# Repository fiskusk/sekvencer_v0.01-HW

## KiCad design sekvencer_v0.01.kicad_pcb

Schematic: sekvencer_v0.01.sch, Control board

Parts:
C1, C2, C4, C5, C9, C10: 10n; C_0805_2012Metric
C3: 47u; CP_Radial_D5.0mm_P2.50mm
C6, C23, C37: 1u; C_0805_2012Metric
C7, C8, C15, C17, C18, C20, C24, C25, C27: 100n; C_0805_2012Metric
C11, C12: 47n; C_0805_2012Metric
C13, C16, C19: 1n; C_0805_2012Metric
C14: 100p; C_0805_2012Metric
C21: 100u; CP_Radial_D10.0mm_P5.00mm
C22: 4u7; C_0805_2012Metric
C26: 470u; CP_Radial_D10.0mm_P5.00mm
C28, C29, C30, C33, C34, C36, C38, C39: NFM21CC223R1H3D; NFM21C_Series
C31, C32: 15p; C_0805_2012Metric
C35: 2u2; C_0805_2012Metric
D1: BAS7002VH6327XTSA1; D_SOD-523
D2: 1N4148; D_SOD-123
D3: LM4040DBZ-2.5; SOT-23
D4, D5: 1N4148; D_MELF
D6: STPS3L60U; D_SMB
D7: STAT1; LED_0805_2012Metric
D8: REL1; LED_0805_2012Metric
D9: REL2; LED_0805_2012Metric
D10: FAN; LED_0805_2012Metric
D11: +5V; LED_0805_2012Metric
D12: PTT; LED_0805_2012Metric
D13: 3.3V; LED_0805_2012Metric
D_50V1: LH R974-LP-1; LED_0805_2012Metric
J1: AVR_ISP_01X06; PinHeader_1x06_P2.54mm_Vertical
J2: PTT; JST_XH_B02B-XH-A_1x02_P2.50mm_Vertical
J3: SWR; JST_XH_B02B-XH-A_1x02_P2.50mm_Vertical
J4: PWR; JST_XH_B02B-XH-A_1x02_P2.50mm_Vertical
J5: LCD; JST_EH_B09B-EH-A_1x09_P2.50mm_Vertical
J6: RX_REL; JST_XH_B02B-XH-A_1x02_P2.50mm_Vertical
J7: TX_REL; JST_XH_B02B-XH-A_1x02_P2.50mm_Vertical
J8: FAN; JST_XH_B02B-XH-A_1x02_P2.50mm_Vertical
J9: 50V_IN; TerminalBlock_KEYS7808
J10: 50V_OUT; TerminalBlock_KEYS7808
J11: BIAS_DIRECT; JST_XH_B02B-XH-A_1x02_P2.50mm_Vertical
J12, J14, J15, J16, J18, J19: 50V_GND; MountingHole_3.2mm_M3_Pad_Via
J13: TERMISTOR; JST_XH_B02B-XH-A_1x02_P2.50mm_Vertical
J17: BIAS; JST_XH_B02B-XH-A_1x02_P2.50mm_Vertical
L1, L2: 470n; L_0805_2012Metric_Pad1.15x1.50mm_HandSolder
L3: 10u; L_0805_2012Metric
L4: DE1209-230u; L_12x12mm_H8mm
L5, L6, L7, L8, L9, L10: BLM31PG500SN1L; C_1206_3216Metric
Q1: BC857; SOT-23
Q2, Q3, Q6: BSS138; SOT-23
Q4: IRLML0030TRPBF; SOT-23
Q5: BBS3002-TL-1E; TO-263-2
Q7: BC847; TO-92
R1, R7, R8, R22: 4k7; R_0805_2012Metric
R2, R6, R9, R21, R26, R34: 1k; R_0805_2012Metric
R3, R14, R16: 10k; R_0805_2012Metric
R4, R5, R17: 22k; R_0805_2012Metric
R10, R11, R12, R18: 100k; R_0805_2012Metric
R13: 499R; R_0805_2012Metric
R15: 270k; R_0805_2012Metric
R19, R20: 0R005; OAR5R010FLF
R23: 100k; R_0402_1005Metric
R25: 1k2; R_0805_2012Metric
R27: 12k; R_0805_2012Metric
R28: 18k; R_0805_2012Metric
R29, R30, R31: 3k9; R_0805_2012Metric
R32: 2k2; R_0805_2012Metric
R33: 10R; R_0805_2012Metric
R35: 220R; R_0805_2012Metric
R36: 470R; R_0805_2012Metric
RV1, RV2, RV3, RV4: 10k; Potentiometer_Bourns_3214J_Horizontal
TP1: ADC_UCC; TestPoint_Pad_D2.0mm
TP2: +5V; TestPoint_Pad_D2.0mm
TP3: +12V; TestPoint_Pad_D2.0mm
TP4: ADC ICC; TestPoint_Pad_D2.0mm
TP5: GND; TestPoint_Pad_D2.0mm
U1: ATmega328P-AU; TQFP-32_7x7mm_P0.8mm
U2: LP2950-5.0_TO252; TO-252-2
U3: LM2576HVS-12; TO-263-5_TabPin3
U4: LTC6101AHS5; SOT-23-5
U5: LP2951ACD-3.3R2G; SOIC-8_3.9x4.9mm_P1.27mm
Y1: LFXTAL071268CUTT 16MHz; Crystal_SMD_2520-4Pin_2.5x2.0mm

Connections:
+2V5: C15.1, D3.1 (K), R2.2, R3.1, U1.20 (AREF)
+12V: C3.1, C7.1, C19.1, C26.1, D4.1 (K), D5.1 (K), D8.2 (A), D9.2 (A), D10.2 (A), J6.2, J7.1, J8.2, L4.2, TP3.1, U2.1 (VI), U3.4 (FB)
+50V: C23.1, C24.1, J9.1, L5.2, L8.1, R19.2, R20.2, U4.5 (V+)
/ADC_ICC: R14.2, TP4.1, U1.19 (ADC6), U4.1 (OUT)
/ADC_PWR: C12.1, R5.1, U1.25 (PC2)
/ADC_SWR: C11.1, R4.1, U1.24 (PC1)
/ADC_TEMP: C34.3, U1.23 (PC0)
/ADC_UCC: C27.1, R15.2, R16.1, TP1.1, U1.22 (ADC7)
/DB4: J5.6, U1.14 (PB2)
/DB5: J1.3 (SCK), J5.7, U1.15 (PB3)
/DB6: J1.4 (~RST), J5.8, U1.16 (PB4)
/DB7: J1.5 (MISO), J5.9, U1.17 (PB5)
/E: J5.5, U1.13 (PB1)
/MCU_BIAS: R23.2, U1.11 (PD7)
/MCU_FAN: Q4.1 (G), R12.1, U1.1 (PD3)
/MCU_PTT: Q1.3 (C), R8.1, R26.2, U1.32 (PD2)
/MCU_REL1: Q6.1 (G), R10.1, U1.27 (PC4)
/MCU_REL2: Q3.1 (G), R11.1, U1.28 (PC5)
/MCU_SUPPLY: Q2.1 (G), R18.1, U1.9 (PD5)
/RESET: J1.6 (MOSI), R6.2, U1.29 (~RESET~/PC6)
/RS: J5.4, U1.12 (PB0)
/STATUS_LED1: R21.2, U1.10 (PD6)
/XTAL1: C31.1, U1.7 (XTAL1/PB6), Y1.3
/XTAL2: C32.1, U1.8 (XTAL2/PB7), Y1.1
GND: C1.2, C2.2, C3.2, C4.2, C5.2, C6.2, C7.2, C8.2, C9.2, C10.2, C11.2, C12.2, C13.2, C14.2, C15.2, C16.2, C17.2, C18.2, C19.2, C20.2, C21.2, C22.2, C23.2, C24.2, C25.2, C26.2, C27.2, C28.2, C29.2, C30.2, C31.2, C32.2, C33.2, C34.2, C35.2, C36.2, C37.1, C38.2, C39.2, D3.2 (A), D6.2 (A), D7.1 (K), D12.1 (K), D13.1 (K), D_50V1.1 (K), J1.2 (GND), J2.2, J3.2, J4.1, J5.2, J11.2, J12.1, J13.1, J14.1, J15.1, J16.1, J17.2, J18.1, J19.1, Q2.2 (S), Q3.2 (S), Q4.2 (S), Q6.2 (S), Q7.2 (E), R8.2, R9.2, R10.2, R11.2, R12.2, R14.1, R16.2, R18.2, R32.2, RV1.3, RV2.3, RV3.3, TP5.1, U1.3 (GND), U1.5 (GND), U1.21 (GND), U2.2 (GND), U3.3 (GND), U3.5 (~ON~/OFF), U4.2 (V-), Y1.2, Y1.4
unnamed: C1.1, C29.3, L1.1
unnamed: C2.1, C30.3, L2.1
unnamed: C4.1, L1.2, RV1.1
unnamed: C5.1, L2.2, RV2.1
unnamed: C9.1, C13.1, C14.1, C20.1, C21.1, C28.3, R15.1, U3.1 (VIN)
unnamed: C18.1, L3.2, U1.18 (AVCC)
unnamed: C28.1, L5.1
unnamed: C29.1, L9.1
unnamed: C30.1, L10.1
unnamed: C33.1, R7.1
unnamed: C33.3, D2.1 (K)
unnamed: C34.1, R17.1
unnamed: C36.1, RV4.2
unnamed: C36.3, L6.2
unnamed: C37.2, R33.1, R34.1, RV4.1
unnamed: C38.1, R13.1
unnamed: C38.3, L8.2
unnamed: C39.1, U4.4 (+)
unnamed: C39.3, L7.2
unnamed: D1.1 (K), J11.1, R23.1, U5.3
unnamed: D1.2 (A), Q7.3 (C), R25.1, R34.2, R35.2, U5.4
unnamed: D2.2 (A), Q1.1 (B), R1.2
unnamed: D4.2 (A), J6.1, Q6.3 (D), R29.2
unnamed: D5.2 (A), J7.2, Q3.3 (D), R30.2
unnamed: D6.1 (K), L4.1, U3.2 (OUT)
unnamed: D7.2 (A), R21.1
unnamed: D8.1 (K), R29.1
unnamed: D9.1 (K), R30.1
unnamed: D10.1 (K), R31.1
unnamed: D11.1 (K), R9.1
unnamed: D12.2 (A), R26.1
unnamed: D13.2 (A), R36.2
unnamed: D_50V1.2 (A), R28.1
unnamed: J2.1, R7.2
unnamed: J3.1, L9.2
unnamed: J4.2, L10.2
unnamed: J5.1, RV3.2
unnamed: J8.1, Q4.3 (D), R31.2
unnamed: J10.1, Q5.2 (D), R28.2
unnamed: J13.2, R3.2, R17.2
unnamed: J17.1, L6.1
unnamed: L7.1, Q5.3 (S), R19.1, R20.1, R22.2
unnamed: Q2.3 (D), R27.1
unnamed: Q5.1 (G), R22.1, R27.2
unnamed: Q7.1 (B), R25.2, R32.1
unnamed: R4.2, RV1.2
unnamed: R5.2, RV2.2
unnamed: R13.2, U4.3 (-)
unnamed: R33.2, R36.1, U5.1, U5.2
unnamed: R35.1, RV4.3
unnamed: U5.6, U5.7

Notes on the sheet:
0,1V @ 40A Pztr 4W
For gain 20 R13 = 499R R14 = 10k
MOSI
MISO
SCK

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
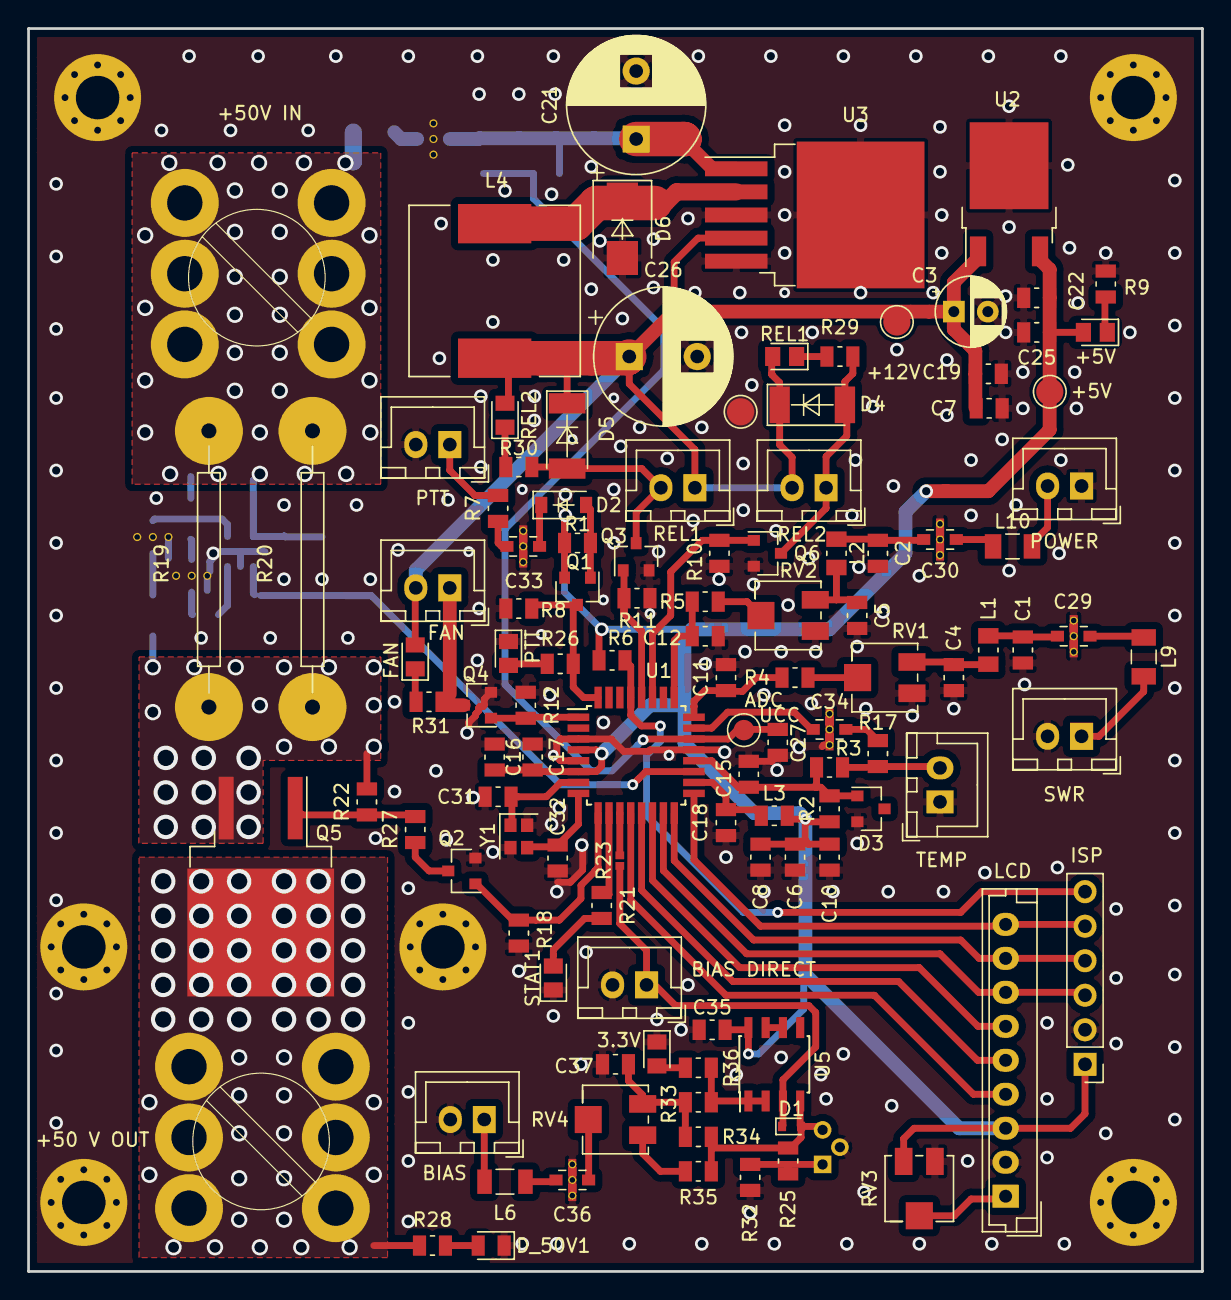
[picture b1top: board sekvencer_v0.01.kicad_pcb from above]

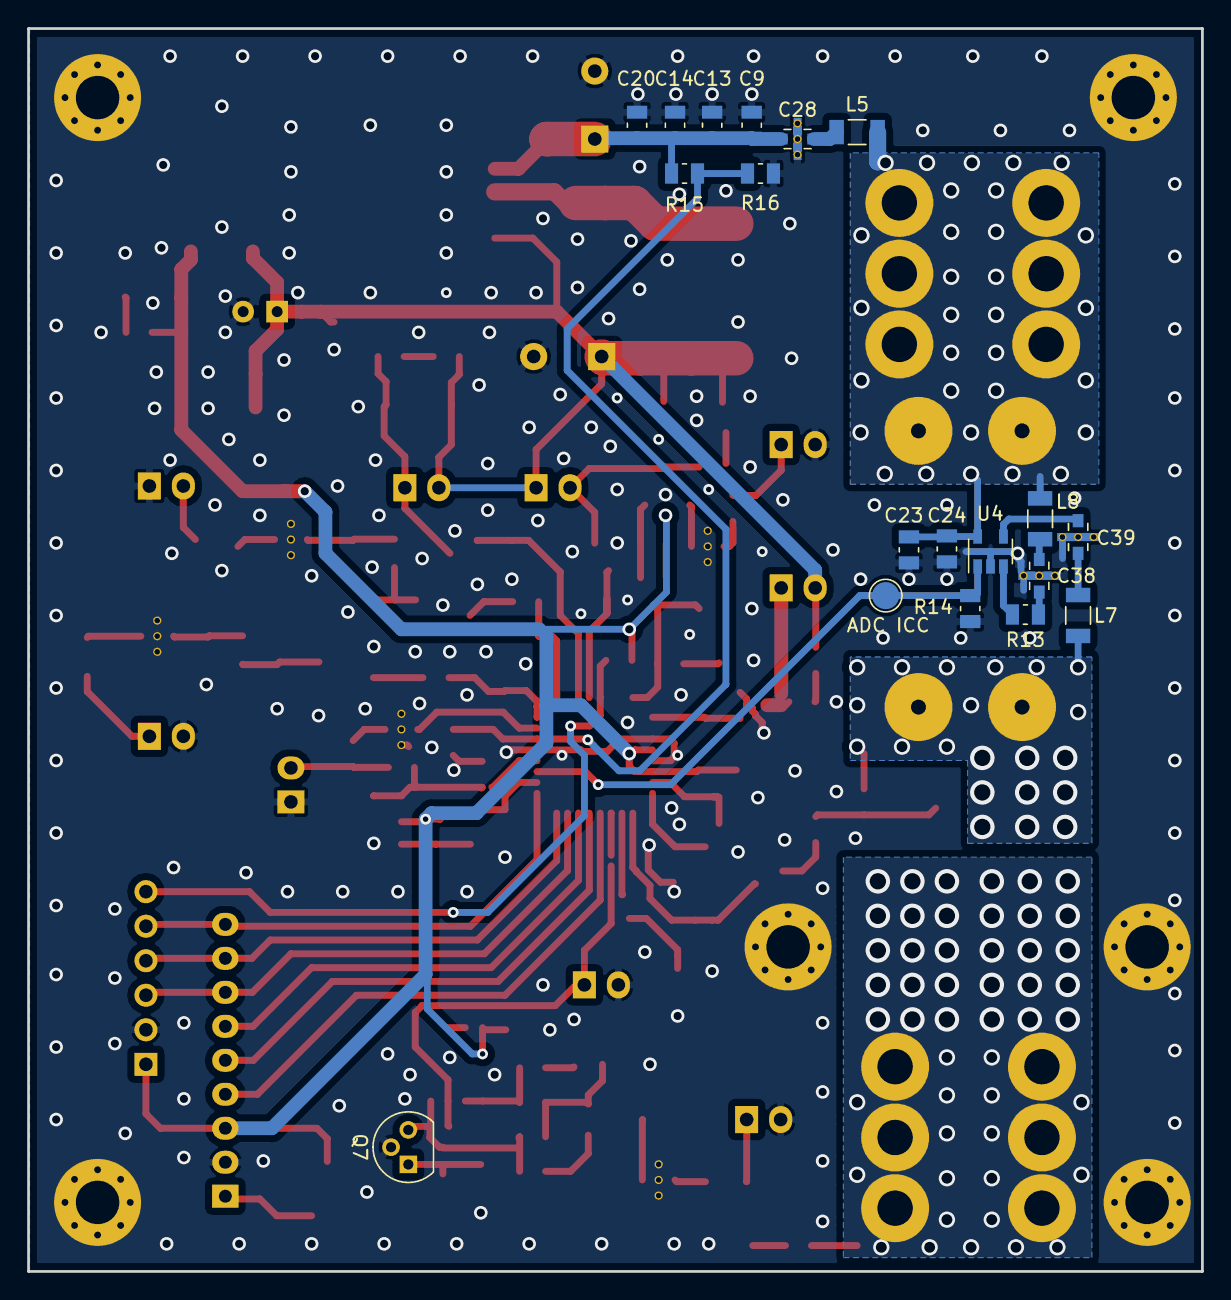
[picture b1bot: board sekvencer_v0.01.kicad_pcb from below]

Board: 2 copper layers, 86.4 x 91.4 mm, 139 parts (19 on the bottom side), 77 nets.

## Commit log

2018-04-03 first version
2018-04-06 refactored second version, added bias circuit, fixed layout
2018-04-08 oficial second version, fixed previous commit
2018-04-10 third version, sent to fabrication in allpcb
2018-04-16 in schematic edit value of any components, added some docs
2018-04-26 added some docs and outputs
2018-05-19 added .gitingnore
2018-05-19 fix gitignore
2018-05-19 first revision, added resistor and diode in bias circuit
2018-05-19 hiearchic
2018-05-19 buigs
2018-05-20 add partial schematics images, complete schematic good version for publi
